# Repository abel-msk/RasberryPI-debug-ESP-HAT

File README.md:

# Raspberry Pi debug ESP HAT

HAT для Raspberry Pi (40-pin), на который ставится плата **ESP32-C3 SuperMini**.
Raspberry Pi может прошивать и отлаживать ESP через UART, управлять её питанием
и режимом загрузки, а все выводы ESP выведены на пружинные клеммники для
подключения внешних проводов.

Проект сделан в **KiCad 10**. Текущая версия платы — **2.1**.

| Версия | Метка в git | Что изменилось |
|--------|-------------|----------------|
| 1   | `v1`   | первая версия: разъём под логический анализатор |
| 2   | `v2`   | пружинные клеммники KF250 (J2, J3), ESP в гнёздах |
| 2.1 | `v2.1` | светодиоды активности GPIO (D2–D11), надпись с версией на плате |

## Возможности

- **Колодка для ESP32-C3 SuperMini.** Два гнезда PLS 1×8 (J4, J5). Модуль с
  впаянными штырями вставляется сверху, его можно снять.
- **Связь с Raspberry Pi.** UART0 Pi ↔ UART ESP, SPI0, несколько GPIO.
  Все линии идут через последовательные резисторы 1 кОм: это защищает от
  конфликта выходов и ограничивает обратное питание ESP, когда она выключена.
- **Управление питанием ESP.** P-MOSFET AO3401A (Q1):
  - по умолчанию питание включено (R16 тянет затвор к земле);
  - GPIO22 = HIGH выключает ESP;
  - SW1 (RESET) — ручной перезапуск по питанию (у C3 SuperMini нет вывода EN).
- **Режим загрузки.** Кнопка BOOT (SW2) на IO9, либо GPIO4 с Pi.
- **Клеммники J2, J3.** KF250-2.54-8P, все выводы ESP выведены на них для внешних
  проводов. Подписи пинов есть на обеих сторонах платы.
- **Светодиоды активности GPIO.** D2–D11, по одному на линии IO0, IO1, IO3–IO7,
  IO10, IO20, IO21. Стоят столбиком между клеммниками и ESP, у каждого подпись
  с номером IO. Цепочка: линия → светодиод → резистор → GND. Синие 0603
  TO-1608BC-BF (Vf ≈ 2.8–3.2 В) с резистором 1 кОм, ток 0.2–0.4 мА.
  На strap-пинах IO2, IO8, IO9 светодиодов нет, чтобы не мешать загрузке ESP.
- **HAT ID EEPROM.** CAT24C256 (U1) на ID_SD/ID_SC. Перемычка JP1 (надпись
  «EEPROM WP») включает защиту от записи, подробнее в разделе
  [«EEPROM HAT и джампер JP1»](#eeprom-hat-и-джампер-jp1).
- **Индикатор питания ESP.** Зелёный светодиод D1 (надпись «PWR»), горит,
  когда включено питание ESP.

## Распиновка

### ESP → Raspberry Pi (через 1 кОм)

| ESP  | Raspberry Pi            | Примечание             |
|------|-------------------------|------------------------|
| IO0  | GPIO23 (pin 16)         |                        |
| IO1  | GPIO24 (pin 18)         |                        |
| IO2  | GPIO5 (pin 29)          | strap, подтяжка на Pi  |
| IO3  | GPIO25 (pin 22)         |                        |
| IO4  | GPIO12 / PWM0 (pin 32)  |                        |
| IO5  | GPIO9 / SPI0.MISO (pin 21) |                     |
| IO6  | GPIO11 / SPI0.SCLK (pin 23) |                    |
| IO7  | GPIO10 / SPI0.MOSI (pin 19) |                    |
| IO8  | GPIO6 (pin 31)          | strap, подтяжка на Pi  |
| IO9  | GPIO4 (pin 7)           | BOOT, подтяжка на Pi   |
| IO10 | GPIO8 / SPI0.CE0 (pin 24) |                      |
| IO20 | GPIO14 / TXD0 (pin 8)   | RX ESP                 |
| IO21 | GPIO15 / RXD0 (pin 10)  | TX ESP                 |
| PWR  | GPIO22 (pin 15)         | 1 = питание ESP выкл.  |

### Клеммники

| Пин | 1   | 2   | 3   | 4   | 5   | 6    | 7    | 8    |
|-----|-----|-----|-----|-----|-----|------|------|------|
| J2 (левый ряд ESP)  | IO5 | IO6 | IO7 | IO8 | IO9 | IO10 | IO20 | IO21 |
| J3 (правый ряд ESP) | IO0 | IO1 | IO2 | IO3 | IO4 | 3V3  | GND  | 5V   |

> **5V на J3-8** — это вывод 5V самой ESP. Он **не соединён** с 5V от Raspberry Pi,
> чтобы USB ESP не запитывал Pi в обратную сторону.

## Прошивка ESP с Raspberry Pi

1. Выключить ESP: `GPIO22 = 1`.
2. Прижать IO9 к земле: `GPIO4 = 0`.
3. Включить ESP: `GPIO22 = 0`. ESP стартует в режиме загрузки.
4. Прошить:

   ```bash
   esptool.py --before no_reset --port /dev/serial0 write_flash 0x0 firmware.bin
   ```

Перед выключением ESP переведите выводы Pi, которые на неё работают, в режим
входа. Иначе ESP будет питаться через IO.

## EEPROM HAT и джампер JP1

На плате стоит EEPROM CAT24C256 (U1) на выводах ID_SD/ID_SC (pin 27/28).
При загрузке Raspberry Pi читает из него описание платы и по нему узнаёт HAT.

Джампер **JP1** (надпись «EEPROM WP») соединяет вывод WP микросхемы с +3V3:

| JP1 | Запись в EEPROM | Чтение (опознание HAT) |
|-----|-----------------|------------------------|
| снят | разрешена (WP подтянут к земле внутри микросхемы) | работает |
| надет | запрещена | работает |

JP1 **не отключает** EEPROM: Pi видит плату как HAT в обоих положениях.
Джампер только защищает содержимое от случайной записи.

### Как прошить EEPROM

Утилиты `eepmake` и `eepflash.sh` лежат в репозитории
[raspberrypi/utils](https://github.com/raspberrypi/utils), папка `eeptools`.

1. **Снять** JP1.
2. Собрать образ из текстового описания платы:

   ```bash
   eepmake eeprom_settings.txt eeprom.eep
   ```

3. Записать образ в EEPROM:

   ```bash
   sudo eepflash.sh -w -f=eeprom.eep -t=24c256
   ```

4. **Надеть** JP1, чтобы закрыть запись.
5. Перезагрузить Pi и проверить, что плата опознана:

   ```bash
   cat /proc/device-tree/hat/product
   ```

### Как сделать, чтобы Pi не считал плату HAT

- Добавить в `/boot/firmware/config.txt` строку `force_eeprom_read=0`.
  Прошивка Pi перестанет читать EEPROM при загрузке. Паять ничего не нужно.
- Или не прошивать EEPROM либо стереть его: без правильной сигнатуры Pi считает,
  что HAT не подключён.
- Или не запаивать U1.

## Файлы

| Файл | Что это |
|------|---------|
| `RasberryPI debug ESP HAT.kicad_pro` / `.kicad_sch` / `.kicad_pcb` | проект KiCad |
| [`schematic.pdf`](schematic.pdf) | схема в PDF |
| [`BOM.csv`](BOM.csv) | перечень элементов |
| `ESP_Debug.pretty/` | посадочное место колодки ESP32-C3 SuperMini |
| `images/` | 3D-рендеры для README |

## Перечень элементов (кратко)

| Обозначение | Номинал | Корпус |
|-------------|---------|--------|
| U2 | ESP32-C3 SuperMini | модуль в гнёздах J4, J5 (PLS 1×8) |
| U1 | CAT24C256 | SOIC-8 |
| Q1 | AO3401A | SOT-23 |
| J1 | гнездо 2×20 для GPIO Pi | 2.54 мм |
| J2, J3 | KF250-2.54-8P (LCSC C49173293) | пружинные клеммники |
| JP1 | перемычка 1×2 | 2.54 мм |
| SW1, SW2 | тактовые кнопки | Omron B3FS-100xP |
| R3–R15, R17, R18 | 1 кОм | 0805 |
| R1, R2 | 3.9 кОм | 0805 |
| R16 | 100 кОм | 0805 |
| C1, C3 / C2 | 100 нФ / 10 мкФ | 0805 |
| D1 | светодиод зелёный (питание ESP) | 0603 |
| D2–D11 | светодиод синий TO-1608BC-BF | 0603 |
| R19–R28 | 1 кОм | 0603 |

Полный список — в [`BOM.csv`](BOM.csv).

> 3D-модели ESP32-C3 SuperMini и клеммников KF250 лежат в пользовательской
> библиотеке (`${KIKAD_USER_3DMODELS}`) и в репозиторий не входят.

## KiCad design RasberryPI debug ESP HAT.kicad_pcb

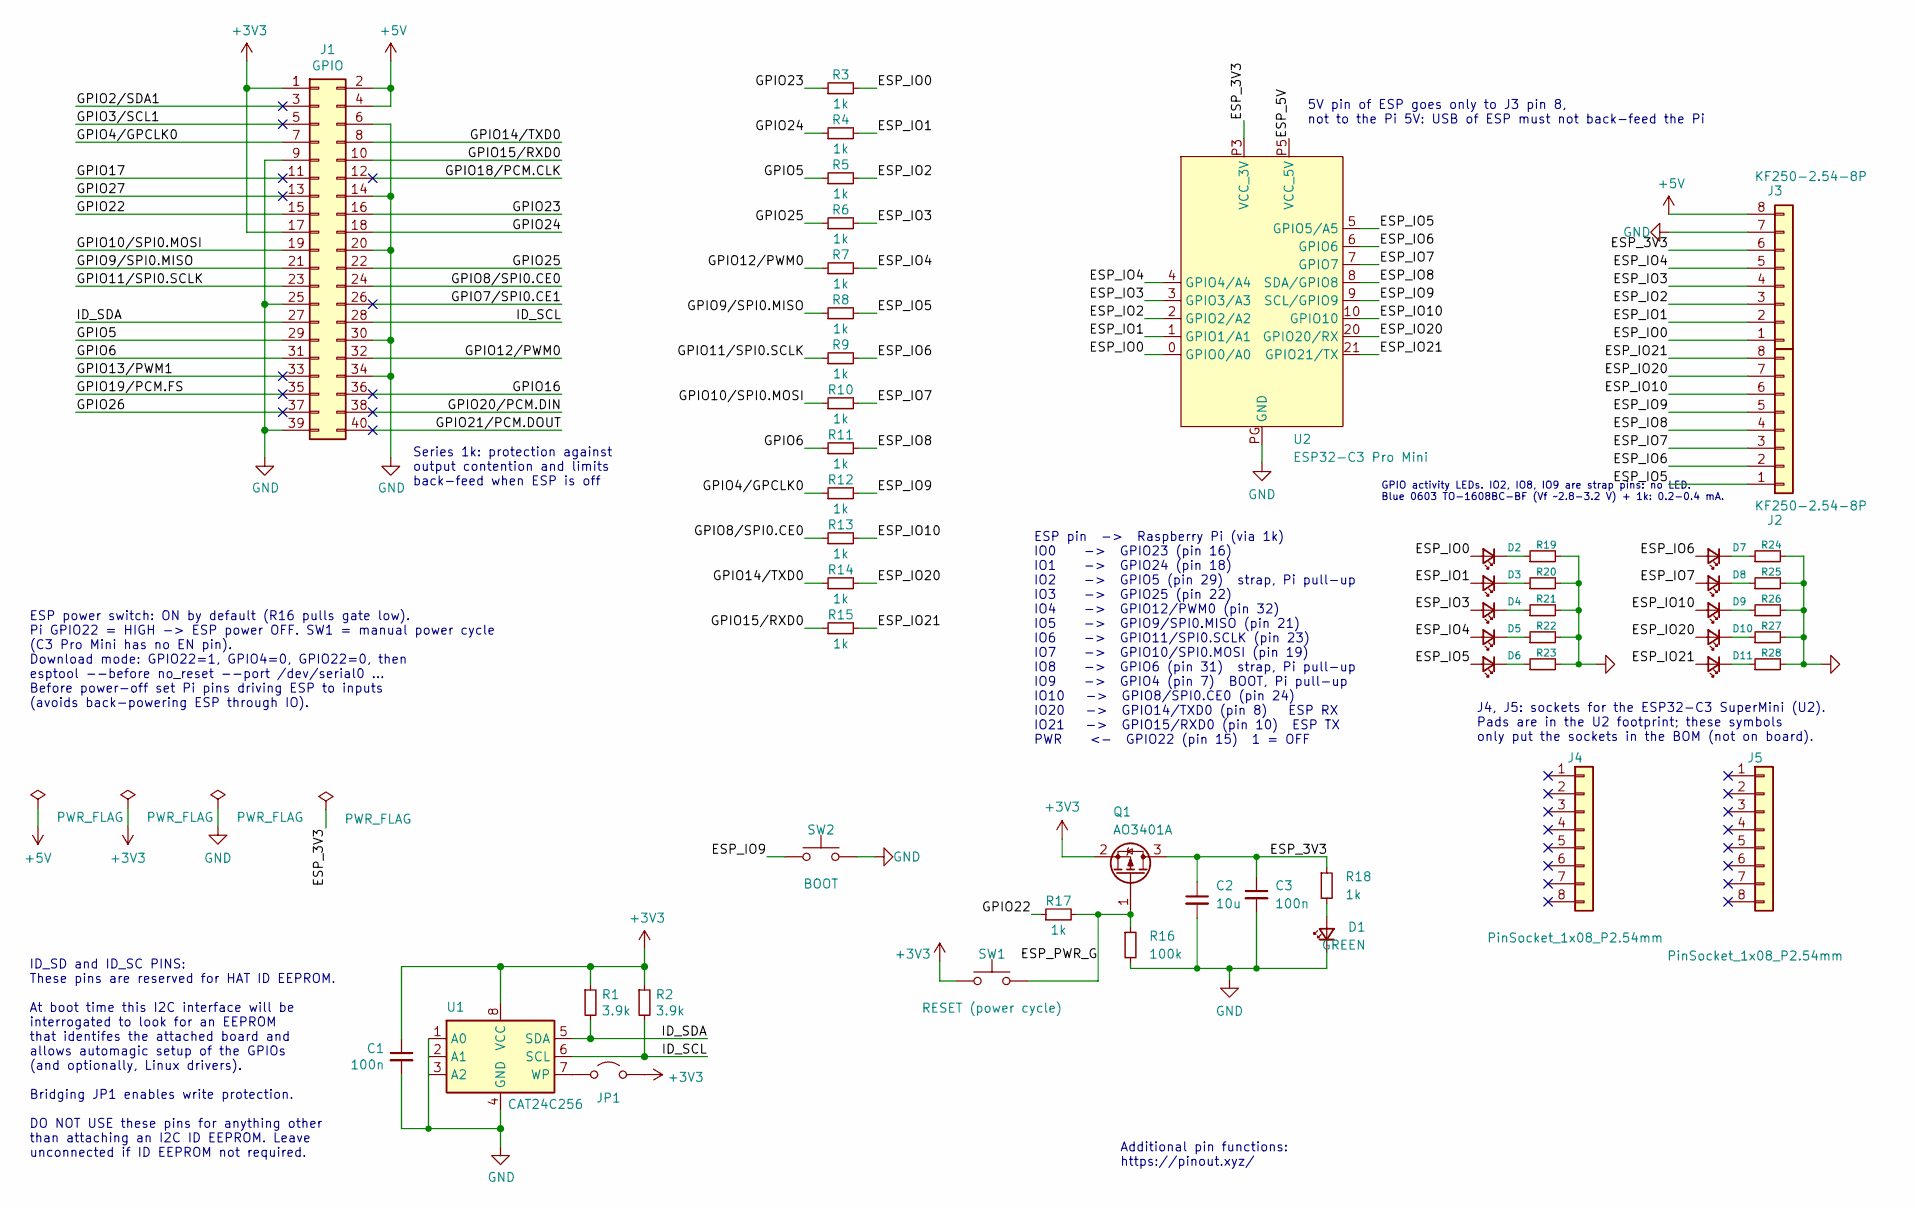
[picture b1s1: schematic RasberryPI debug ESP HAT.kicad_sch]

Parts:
C1, C3: 100n; C_0805_2012Metric_Pad1.18x1.45mm_HandSolder
C2: 10u; C_0805_2012Metric_Pad1.18x1.45mm_HandSolder
D1: GREEN; LED_0603_1608Metric_Pad1.05x0.95mm_HandSolder
D2, D3, D4, D5, D6, D7, D8, D9, D10, D11: BLUE; LED_0603_1608Metric
J1: GPIO; PinSocket_2x20_P2.54mm_Vertical
J2, J3: KF250-2.54-8P
J4, J5: PinSocket_1x08_P2.54mm; PinSocket_1x08_P2.54mm_Vertical
JP1: ID_WP; PinHeader_1x02_P2.54mm_Vertical
Q1: AO3401A; SOT-23
R1, R2: 3.9k; R_0805_2012Metric_Pad1.20x1.40mm_HandSolder
R3, R4, R5, R6, R7, R8, R9, R10, R11, R12, R13, R14, R15, R17, R18: 1k; R_0805_2012Metric_Pad1.20x1.40mm_HandSolder
R16: 100k; R_0805_2012Metric_Pad1.20x1.40mm_HandSolder
R19, R20, R21, R22, R23, R24, R25, R26, R27, R28: 1k; R_0603_1608Metric
SW1: RESET (power cycle); SW_SPST_Omron_B3FS-100xP
SW2: BOOT; SW_SPST_Omron_B3FS-100xP
U1: CAT24C256; SOIC-8_3.9x4.9mm_P1.27mm
U2: ESP32-C3 Pro Mini; ESP32-C3_Pro_mini_socket

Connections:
+3V3: C1.1, J1.1, J1.17, JP1.2 (B), Q1.2 (S), R1.1, R2.1, SW1.1, U1.8 (VCC)
+5V: J1.2, J1.4, J3.8
/ESP_3V3: C2.1, C3.1, J3.6, Q1.3 (D), R18.1, U2.P3 (VCC_3V)
/ESP_5V: U2.P5 (VCC_5V)
/ESP_IO0: D2.2 (A), J3.1, R3.2, U2.0 (GPIO0/A0)
/ESP_IO1: D3.2 (A), J3.2, R4.2, U2.1 (GPIO1/A1)
/ESP_IO2: J3.3, R5.2, U2.2 (GPIO2/A2)
/ESP_IO3: D4.2 (A), J3.4, R6.2, U2.3 (GPIO3/A3)
/ESP_IO4: D5.2 (A), J3.5, R7.2, U2.4 (GPIO4/A4)
/ESP_IO5: D6.2 (A), J2.1, R8.2, U2.5 (GPIO5/A5)
/ESP_IO6: D7.2 (A), J2.2, R9.2, U2.6 (GPIO6)
/ESP_IO7: D8.2 (A), J2.3, R10.2, U2.7 (GPIO7)
/ESP_IO8: J2.4, R11.2, U2.8 (SDA/GPIO8)
/ESP_IO9: J2.5, R12.2, SW2.1, U2.9 (SCL/GPIO9)
/ESP_IO10: D9.2 (A), J2.6, R13.2, U2.10 (GPIO10)
/ESP_IO20: D10.2 (A), J2.7, R14.2, U2.20 (GPIO20/RX)
/ESP_IO21: D11.2 (A), J2.8, R15.2, U2.21 (GPIO21/TX)
/ESP_PWR_G: Q1.1 (G), R16.1, R17.2, SW1.2
/GPIO2/SDA1: J1.3
/GPIO3/SCL1: J1.5
/GPIO4/GPCLK0: J1.7, R12.1
/GPIO5: J1.29, R5.1
/GPIO6: J1.31, R11.1
/GPIO7/SPI0.CE1: J1.26
/GPIO8/SPI0.CE0: J1.24, R13.1
/GPIO9/SPI0.MISO: J1.21, R8.1
/GPIO10/SPI0.MOSI: J1.19, R10.1
/GPIO11/SPI0.SCLK: J1.23, R9.1
/GPIO12/PWM0: J1.32, R7.1
/GPIO13/PWM1: J1.33
/GPIO14/TXD0: J1.8, R14.1
/GPIO15/RXD0: J1.10, R15.1
/GPIO16: J1.36
/GPIO17: J1.11
/GPIO18/PCM.CLK: J1.12
/GPIO19/PCM.FS: J1.35
/GPIO20/PCM.DIN: J1.38
/GPIO21/PCM.DOUT: J1.40
/GPIO22: J1.15, R17.1
/GPIO23: J1.16, R3.1
/GPIO24: J1.18, R4.1
/GPIO25: J1.22, R6.1
/GPIO26: J1.37
/GPIO27: J1.13
/ID_SCL: J1.28, R2.2, U1.6 (SCL)
/ID_SDA: J1.27, R1.2, U1.5 (SDA)
GND: C1.2, C2.2, C3.2, D1.1 (K), J1.6, J1.9, J1.14, J1.20, J1.25, J1.30, J1.34, J1.39, J3.7, R16.2, R19.2, R20.2, R21.2, R22.2, R23.2, R24.2, R25.2, R26.2, R27.2, R28.2, SW2.2, U1.1 (A0), U1.2 (A1), U1.3 (A2), U1.4 (GND), U2.PG (GND)
unnamed: D1.2 (A), R18.2
unnamed: D2.1 (K), R19.1
unnamed: D3.1 (K), R20.1
unnamed: D4.1 (K), R21.1
unnamed: D5.1 (K), R22.1
unnamed: D6.1 (K), R23.1
unnamed: D7.1 (K), R24.1
unnamed: D8.1 (K), R25.1
unnamed: D9.1 (K), R26.1
unnamed: D10.1 (K), R27.1
unnamed: D11.1 (K), R28.1
unnamed: JP1.1 (A), U1.7 (WP)

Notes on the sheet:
Series 1k: protection against output contention and limits back-feed when ESP is off
J4, J5: sockets for the ESP32-C3 SuperMini (U2). Pads are in the U2 footprint; these symbols only put the sockets in the BOM (not on board).
Additional pin functions: https://pinout.xyz/
ESP pin -> Raspberry Pi (via 1k) IO0 -> GPIO23 (pin 16) IO1 -> GPIO24 (pin 18) IO2 -> GPIO5 (pin 29) strap, Pi pull-up IO3 -> GPIO25 (pin 22) IO4 -> GPIO12/PWM0 (pin 32) IO5 -> GPIO9/SPI0.MISO (pin 21) IO6 -> GPIO11/SPI0.SCLK (pin 23) IO7 -> GPIO10/SPI0.MOSI (pin 19) IO8 -> GPIO6 (pin 31) strap, Pi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
ESP power switch: ON by default (R16 pulls gate low). Pi GPIO22 = HIGH -> ESP power OFF. SW1 = manual power cycle (C3 Pro Mini has no EN pin). Download mode: GPIO22=1, GPIO4=0, GPIO22=0, then esptool --before no_reset --port /dev/serial0 ... Before power-off set Pi pins driving ESP to inputs (avoid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
5V pin of ESP goes only to J3 pin 8, not to the Pi 5V: USB of ESP must not back-feed the Pi
GPIO activity LEDs. IO2, IO8, IO9 are strap pins: no LED. Blue 0603 TO-1608BC-BF (Vf ~2.8-3.2 V) + 1k: 0.2-0.4 mA.
ID_SD and ID_SC PINS: These pins are reserved for HAT ID EEPROM. At boot time this I2C interface will be interrogated to look for an EEPROM that identifes the attached board and allows automagic setup of the GPIOs (and optionally, Linux drivers). Bridging JP1 enables write protection. DO NOT USE th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

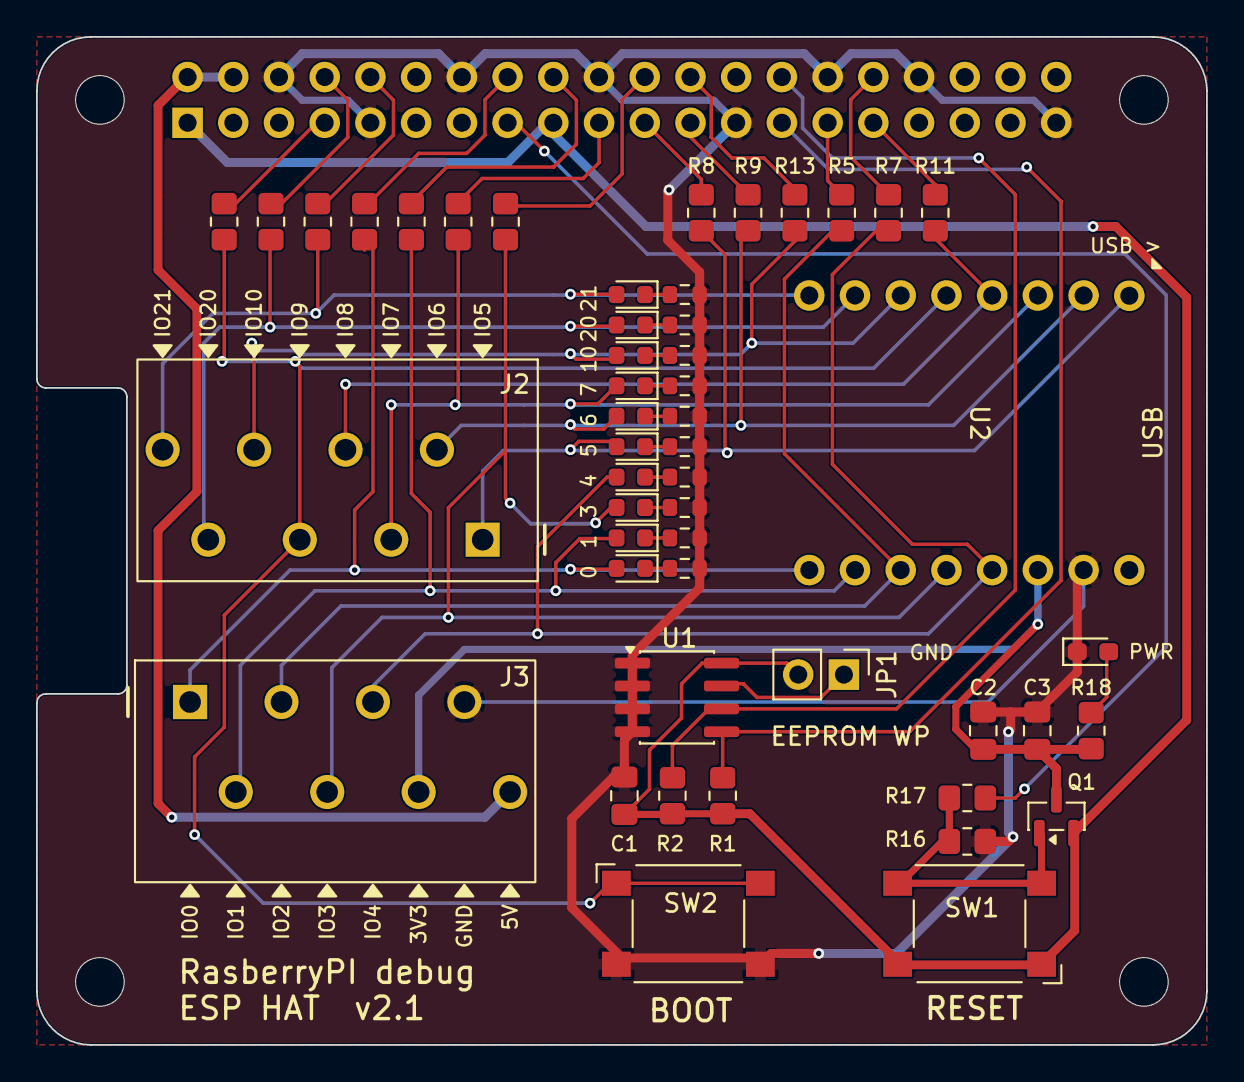
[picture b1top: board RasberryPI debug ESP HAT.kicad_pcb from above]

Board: 2 copper layers, 65.0 x 56.0 mm, 55 parts (1 on the bottom side), 46 nets.

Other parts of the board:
MH1, MH2, MH3, MH4: MountingHole_2.7mm_M2.5

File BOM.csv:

"Обозначения","Номинал","Корпус","Кол-во","DNP","Описание"
"C1,C3","100n","Capacitor_SMD:C_0805_2012Metric_Pad1.18x1.45mm_HandSolder","2","","Unpolarized capacitor, small symbol"
"C2","10u","Capacitor_SMD:C_0805_2012Metric_Pad1.18x1.45mm_HandSolder","1","",""
"D1","PWR","LED_SMD:LED_0603_1608Metric_Pad1.05x0.95mm_HandSolder","1","",""
"D2-D11","GREEN","LED_SMD:LED_0603_1608Metric","10","","LED 0603 green, GPIO activity"
"J1","GPIO","Connector_PinSocket_2.54mm:PinSocket_2x20_P2.54mm_Vertical","1","","Generic connector, double row, 02x20, odd/even pin numbering scheme (row 1 odd numbers, row 2 even numbers), script generated (kicad-library-utils/schlib/autogen/connector/)"
"J2,J3","KF250-2.54-8P","TerminalBlock_Local:KF250-2.54-8P","2","","Spring terminal block KF250-2.54-8P-1 (LCSC C49173293), ESP left row: IO5..IO10, IO20, IO21 (pin 8 = IO21),Spring terminal block KF250-2.54-8P-1 (LCSC C49173293), ESP right row: IO0..IO4, 3V3, GND, ESP 5V (pin 8)"
"J4,J5","PinSocket_1x08_P2.54mm","Connector_PinSocket_2.54mm:PinSocket_1x08_P2.54mm_Vertical","2","","Female pin header 1x8, 2.54 mm, vertical, socket for U2 ESP32-C3 SuperMini; BOM only, part of U2 footprint"
"JP1","ID_WP","Connector_PinHeader_2.54mm:PinHeader_1x02_P2.54mm_Vertical","1","","Jumper, 2-pole, open (2-pin header)"
"Q1","AO3401A","Package_TO_SOT_SMD:SOT-23","1","",""
"R1,R2","3.9k","Resistor_SMD:R_0805_2012Metric_Pad1.20x1.40mm_HandSolder","2","","Resistor, small symbol"
"R3-R15,R17,R18","1k","Resistor_SMD:R_0805_2012Metric_Pad1.20x1.40mm_HandSolder","15","",""
"R16","100k","Resistor_SMD:R_0805_2012Metric_Pad1.20x1.40mm_HandSolder","1","",""
"R19-R28","1k","Resistor_SMD:R_0603_1608Metric","10","","LED current limit, 0603"
"SW1","RESET (power cycle)","SW_SPST_Omron_B3FS-100xP","1","",""
"SW2","BOOT","SW_SPST_Omron_B3FS-100xP","1","",""
"U1","CAT24C256","Package_SO:SOIC-8_3.9x4.9mm_P1.27mm","1","","256 kb CMOS Serial EEPROM, DIP-8/SOIC-8/TSSOP-8/DFN-8"
"U2","ESP32-C3 Pro Mini","ESP_Debug:ESP32-C3_Pro_mini_socket","1","",""
